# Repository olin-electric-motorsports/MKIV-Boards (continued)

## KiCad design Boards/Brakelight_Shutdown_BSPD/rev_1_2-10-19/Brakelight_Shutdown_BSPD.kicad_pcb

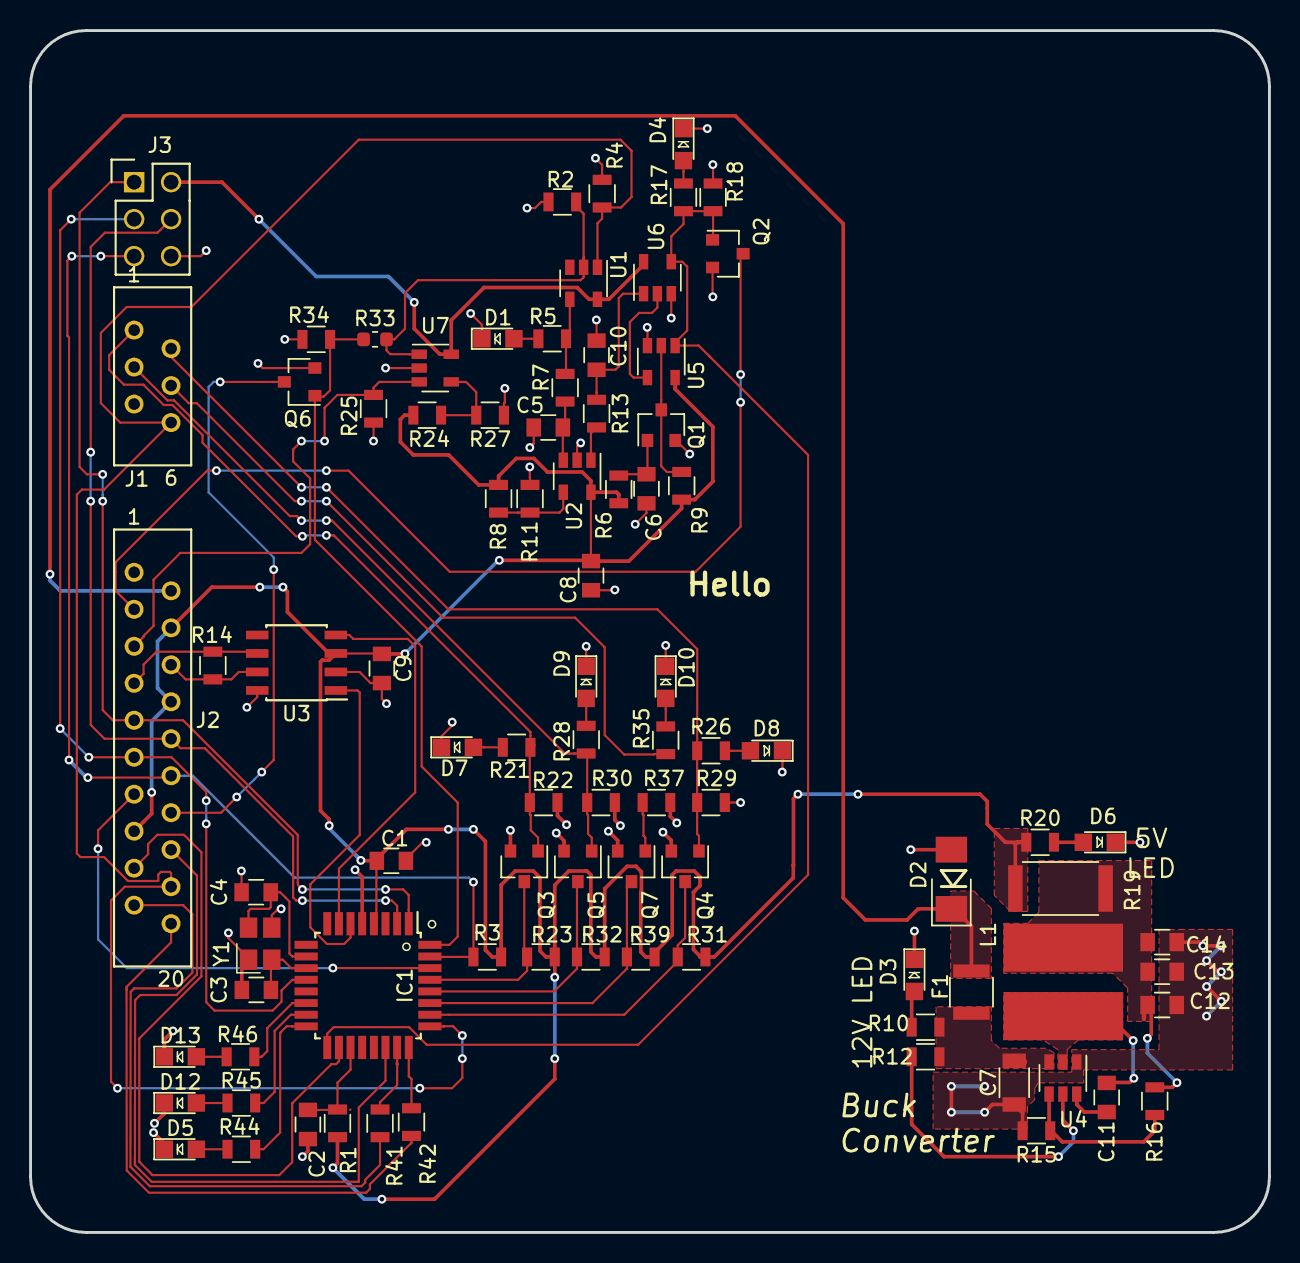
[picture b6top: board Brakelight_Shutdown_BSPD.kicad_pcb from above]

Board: 2 copper layers, 85.1 x 82.6 mm, 89 parts (0 on the bottom side), 65 nets.

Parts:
C1, C6, C8, C9, C11, C14: C_0.1uF; C_0805_OEM
C2: C_100pF; C_0805_OEM
C3, C4: C_30pF; C_0805_OEM
C5: C_10uF; C_0805_OEM
C7: C_22uF; C_1206_OEM
C10, C13: C_1uF; C_0805_OEM
C12: C_47uF; C_0805_OEM
D1, D3, D4, D5, D6, D7, D8, D9, D10, D12, D13: LED_0805; LED_0805_OEM
D2: D_Zener_18V; DO-214AA
F1: 500mA; Fuse_1210
IC1: ATMEGA16M1; TQFP-32_7x7mm_Pitch0.8mm
J1: MM_F_RA_06; micromatch_female_ra_6
J2: MM_F_RA_20; micromatch_female_ra_20
J3: CONN_02X03; Pin_Header_Straight_2x03
L1: L_4.7uH; 4.7uH_Inductor_OEM
Q1, Q2, Q3, Q4, Q5, Q6, Q7: SSM3K333R; SOT-23F
R1: R_100; R_0805_OEM
R2, R4, R9, R22, R29, R30, R37: R_100K; R_0805_OEM
R3, R12, R15: R_10k; R_0805_OEM
R5, R14, R17, R20, R41, R42, R44, R45, R46: R_200; R_0805_OEM
R6, R8, R11, R13, R18, R23, R24, R25, R27, R31, R32, R34, R39: R_10K; R_0805_OEM
R7: R_71.5K; R_0805_OEM
R10: R_1k; R_0805_OEM
R16: R_51.1k; R_0805_OEM
R19: R_0_Jumper; R_2512_OEM
R21, R26, R28, R35: R_1K; R_0805_OEM
R33: R_0; R_0603_1608Metric
U1: SN74LVC1G08; SOT-23-5_OEM
U2, U7: MCP6001; SOT-23-5_OEM
U3: CAN_Transceiver; SOIC-8_3.9x4.9mm_Pitch1.27mm_OEM
U4: TPS561201; SOT-23-6_OEM
U5, U6: SN74LVC1G02; SOT-23-5_OEM
Y1: Crystal_SMD; Crystal_SMD_FA238

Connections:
+12V: D2.1, F1.1, J2.2
/12V_Fused: C7.1, F1.2, R10.1, R12.1, U4.3
/BSPD_Current_Sense: IC1.25, J1.6, J2.18, R4.2, U1.1
/BSPD_Relay: J2.3, Q2.3
/BSPD_Relay_Sense: IC1.17, Q2.1, R17.1, R18.1, U5.1, U6.4
/Brake_Pressure-: IC1.18, J2.17
/Brake_Pressure_Sense: IC1.22, J2.16
/Brake_Switch-: J2.5, R25.2, U7.3
/Brake_Switch_Pressed: R2.1, R33.2, U1.2, U7.1
/Brakelight_Gate: IC1.32, Q6.1, R33.1, R34.1
/Brakelight_LSD: J2.14, Q6.3
/CAN_high: J2.6, R14.1, U3.7
/CAN_low: J2.7, R14.2, U3.6
/Cooling_Pump_LSD_n: IC1.30, J2.13
/LED_1: IC1.14, R46.1
/LED_2: IC1.15, R45.1
/LED_3: IC1.16, R44.1
/MISO: IC1.1, J2.9, J3.1
/MOSI: IC1.2, J2.10, J3.4
/RESET: IC1.31, J2.12, J3.5, R3.2
/RJ45_LED1: J2.19, R41.1
/RJ45_LED2: J2.20, R42.2
/RXCAN: IC1.7, U3.4
/SCK: IC1.12, J2.11, J3.3
/SS_BSPD_Pin: IC1.28, Q5.3, R32.2
/SS_E-Stop_Pin: IC1.26, Q4.3, R31.2
/SS_Main_Shutdown_Pin: IC1.29, Q3.3, R23.2
/SS_TSMS_Pin: IC1.27, Q7.3, R39.2
/Shutdown_Sense_BSPD: J1.3, Q5.1, R28.1, R30.1
/Shutdown_Sense_Estop: J1.2, Q4.1, R26.1, R29.1
/Shutdown_Sense_GLVMS: J1.1, Q3.1, R21.1, R22.1
/Shutdown_Sense_TSMS: J1.4, Q7.1, R35.1, R37.1
/TXCAN: IC1.6, U3.1
GND: C1.2, C2.2, C3.2, C4.2, C5.2, C6.2, C7.2, C8.2, C9.2, C10.2, C12.2, C13.2, C14.2, D1.1, D2.2, D3.1, D4.1, D5.1, D6.1, D7.1, D8.1, D9.1, D10.1, D12.1, D13.1, IC1.5, IC1.20, J2.1, J3.6, Q1.2, Q2.2, Q3.2, Q4.2, Q5.2, Q6.2, Q7.2, R2.2, R4.1, R11.2, R15.2, R18.2, R22.2, R25.1, R27.1, R29.2, R30.2, R34.2, R37.2, U1.3, U2.2, U3.2, U3.8, U4.1, U5.3, U6.3, U7.2, Y1.2, Y1.4
unnamed: C2.1, IC1.19, R1.2
unnamed: C3.1, IC1.11, Y1.1
unnamed: C4.1, IC1.10, Y1.3
unnamed: C5.1, R7.2, U2.3
unnamed: C6.1, Q1.1, R6.2
unnamed: C10.1, R13.1, U6.1
unnamed: C11.1, U4.6
unnamed: C11.2, L1.1, U4.2
unnamed: C12.1, C13.1, C14.1, L1.2, R16.2, R19.2
unnamed: D1.2, R5.2
unnamed: D3.2, R10.2
unnamed: D4.2, R17.2
unnamed: D5.2, R44.2
unnamed: D6.2, R20.2
unnamed: D7.2, R21.2
unnamed: D8.2, R26.2
unnamed: D9.2, R28.2
unnamed: D10.2, R35.2
unnamed: D12.2, R45.2
unnamed: D13.2, R46.2
unnamed: IC1.23, R41.2
unnamed: IC1.24, R42.1
unnamed: Q1.3, R9.1, U5.2
unnamed: R5.1, R7.1, U1.4
unnamed: R8.2, R11.1, U2.4
unnamed: R12.2, U4.5
unnamed: R13.2, U2.1
unnamed: R15.1, R16.1, U4.4
unnamed: R24.1, R27.2, U7.4
unnamed: U5.4, U6.2
VCC: C1.1, C8.1, C9.1, IC1.4, J2.4, J2.8, J2.15, J3.2, R1.1, R3.1, R6.1, R8.1, R9.2, R19.1, R20.1, R23.1, R24.2, R31.1, R32.1, R39.1, U1.5, U2.5, U3.3, U5.5, U6.5, U7.5

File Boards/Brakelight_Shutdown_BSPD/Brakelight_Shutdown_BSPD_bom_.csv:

Component,Description,Part,References,Value,Footprint,Quantity Per PCB,Datasheet,Package,MPN,MFN,PurchasingLink
1,"Capacitor, 0.1uF, 50V, 5%, 0805",C_0.1uF,C1 C6 C8 C9 C11 C14,C_0.1uF,C_0805_OEM,6,http://datasheets.avx.com/X7RDielectric.pdf,Value,478-3352-1-ND,Digi-Key DK,https://www.digikey.com/products/en?keywords=478-3352-1-ND
2,"Capacitor, 100pF, 50V, 5%, 0805",C_100pF,C2,C_100pF,C_0805_OEM,1,https://content.kemet.com/datasheets/KEM_C1003_C0G_SMD.pdf,Value,399-1122-1-ND,Digi-Key,https://www.digikey.com/product-detail/en/kemet/C0805C101J5G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
3,"Capacitor, 10uF, 10V, 10%, 0805",C_10uF,C5,C_10uF,C_0805_OEM,1,http://www.samsungsem.com/kr/support/product-search/mlcc/__i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,,1276-1052-1-ND,DK,https://www.digikey.com/product-detail/en/samsung-electro-me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
4,"Capacitor, 1uF, 25V, 10%, 0805",C_1uF,C10 C13,C_1uF,C_0805_OEM,2,http://www.samsungsem.com/kr/support/product-search/mlcc/__i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,Value,1276-2887-1-ND 478-10487-1-ND,DK Digi-Key,https://www.digikey.com/product-detail/en/samsung-electro-me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 https://www.digikey.com/product-detail/en/avx-corporation/08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
5,"Capacitor, 22uF, 16V, 20%, 1206",C_22uF,C7,C_22uF,C_1206_OEM,1,http://www.samsungsem.com/kr/support/product-search/mlcc/__i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,Value,1276-2725-1-ND,Digi-Key,https://www.digikey.com/products/en?keywords=1276-2725-1-ND
6,"Capacitor, 30pF, 50V, 5%, 0805",C_30pF,C3 C4,C_30pF,C_0805_OEM,2,https://media.digikey.com/pdf/Data%20Sheets/Samsung%20PDFs/C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,Value,1276-1130-1-ND,Digi-Key,https://www.digikey.com/product-detail/en/samsung-electro-me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
7,"Capacitor, 47uF, 6.3V, 20%, 0805",C_47uF,C12,C_47uF,C_0805_OEM,1,http://www.yuden.co.jp/productdata/catalog/en/mlcc_all_e.pdf,Value,587-4280-1-ND,Digi-Key,https://www.digikey.com/product-detail/en/taiyo-yuden/JMK212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
8,"Diode, Zener, 18V, 5W, 5%",D_Zener_18V,D2,D_Zener_18V,DO-214AA,1,http://www.mccsemi.com/up_pdf/SMBJ5338B-SMBJ5388B(SMB).pdf,DO-214AA (SMB),SMBJ5355B-TPMSCT-ND,Digi-Key,https://www.digikey.com/products/en?keywords=SMBJ5355B-TPMSCT-ND
9,"LED, Green, 2.2V, 20mA, 0805",LED_0805,D1 D3 D4 D5 D6 D7 D8 D9 D10 D11 D12 D13,LED_0805,LED_0805_OEM,12,http://www.osram-os.com/Graphics/XPic9/00078860_0.pdf,Value,475-1410-1-ND,DK Digi-Key,https://www.digikey.com/products/en?keywords=475-1410-1-ND
10,"Fuse, PTC, 500mA, 16V, 1210",F_500mA_16V,F1,500mA,Fuse_1210,1,https://belfuse.com/resources/CircuitProtection/datasheets/0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,Value,507-1786-1-ND,Digi-Key,https://www.digikey.com/product-detail/en/bel-fuse-inc/0ZCH0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
11,"Microcontroller, 8-bit, 1KB RAM, 16KB Flash",ATMEGA16M1,IC1,ATMEGA16M1,TQFP-32_7x7mm_Pitch0.8mm,1,http://www.atmel.com/Images/Atmel-8209-8-bit%20AVR%20ATmega1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,Value,ATMEGA16M1-AU-ND,Digi-Key,https://www.digikey.com/product-detail/en/atmel/ATMEGA16M1-A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
12,"Connector header through hole 2x3 0.100"" (2.54mm)",CONN_02X03,J3,CONN_02X03,Pin_Header_Straight_2x03,1,http://portal.fciconnect.com/Comergent//fci/drawing/67996.pdf,Value,609-3234-ND,Digi-Key,https://www.digikey.com/product-detail/en/amphenol-fci/67997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
13,Micro-MaTch connector 6 pin female right angle,MM_F_RA_06,J1,MM_F_RA_06,micromatch_female_ra_6,1,http://www.te.com/commerce/DocumentDelivery/DDEController?Ac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,,338070-6,TE,http://www.te.com/usa-en/product-338070-6.html
14,Micro-MaTch connector 20 pin female right angle,MM_F_RA_20,J2,MM_F_RA_20,micromatch_female_ra_20,1,http://www.te.com/commerce/DocumentDelivery/DDEController?Ac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,,2-338070-0,TE,http://www.te.com/usa-en/product-2-338070-0.html
15,"Inductor, 4.7uH, 4.4A, 25mOhm, 20%",L_4.7uH,L1,L_4.7uH,4.7uH_Inductor_OEM,1,https://product.tdk.com/info/en/documents/wdcatalog/withdraw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,Value,445-6583-1-ND,Digi-Key,https://www.digikey.com/product-detail/en/tdk-corporation/VL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
16,"MOSFET, N-channel, 30V, 6A",SSM3K333R,Q1 Q2 Q3 Q4 Q5 Q6 Q7,SSM3K333R,SOT-23F,7,https://drive.google.com/drive/folders/0B-V-iZf33Y4GNzhDQTJZanJRbVk,,SSM3K333RLFCT-ND,DK,https://www.digikey.com/product-detail/en/toshiba-semiconduc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
17,"Resistor, 0 ohm jumper, 0.1W, 0603",R_0,R33,R_0,R_0603_1608Metric,1,http://industrial.panasonic.com/www-cgi/jvcr13pz.cgi?E+PZ+3+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,,P0.0GCT-ND,DK,https://www.digikey.com/product-detail/en/panasonic-electron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
18,"Resistor, 0 ohm jumper, 0.1W, 0603",R_0,R19,R_0_Jumper,R_2512_OEM,1,http://www.te.com/commerce/DocumentDelivery/DDEController?Ac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,Value,A121322CT-ND,Digi-Key,https://www.digikey.com/products/en?keywords=A121322CT-ND
19,"Resistor, 100, 0.25W, 1%, 0805",R_100,R1,R_100,R_0805_OEM,1,https://www.seielect.com/Catalog/SEI-rncp.pdf,Value,RNCP0805FTD100RCT-ND,Digi-Key,https://www.digikey.com/products/en?keywords=RNCP0805FTD100RCT-ND
20,"Resistor, 100K, 0.125W, 1%, 0805",R_100K,R2 R4 R9 R22 R29 R30 R37,R_100K,R_0805_OEM,7,https://industrial.panasonic.com/cdbs/www-data/pdf/RDA0000/A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,,P100KCCT-ND,DK,https://www.digikey.com/product-detail/en/panasonic-electron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
21,"Resistor, 10K, 0.25W, 1%, 0805",R_10K,R3 R6 R8 R11 R13 R18 R23 R24 R25 R27 R31 R32 R34 R39,R_10k,R_0805_OEM,14,http://www.bourns.com/data/global/pdfs/CRS.pdf,Value,CRS0805-FX-1002ELFCT-ND,Digi-Key DK,https://www.digikey.com/products/en?keywords=CRS0805-FX-1002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
22,"Resistor, 10K, 5W, 1%, Axial",R_10K_HV,R12 R15,R_10k,R_0805_OEM,2,http://www.bourns.com/data/global/pdfs/CRS.pdf,Value,CRS0805-FX-1002ELFCT-ND,Digi-Key,https://www.digikey.com/products/en?keywords=CRS0805-FX-1002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
23,,R_1K-formula,R36,R_1K-formula,R_0805_OEM,1,https://www.seielect.com/Catalog/SEI-rncp.pdf,,RNCP0805FTD1K00CT-ND,DK,https://www.digikey.com/products/en?keywords=RNCP0805FTD1K00CT-ND
24,"Resistor, 1K, 0.25W, 1%, 0805",R_1K,R10 R21 R26 R28 R35,R_1k,R_0805_OEM,5,https://www.seielect.com/Catalog/SEI-rncp.pdf,Value,RNCP0805FTD1K00CT-ND,Digi-Key DK,https://www.digikey.com/products/en?keywords=RNCP0805FTD1K00CT-ND
25,"Resistor, 200, 0.125W, 5%, 0805",R_200,R5 R14 R17 R20 R41 R42 R44 R45 R46,R_200,R_0805_OEM,9,https://www.seielect.com/Catalog/SEI-RMCF_RMCP.pdf,Value,RMCF0805JT200RCT-ND,DK Digi-Key,https://www.digikey.com/products/en?keywords=RMCF0805JT200RCT-ND
26,"Resistor, 51.1K, 0.125W, 1%, 0805",R_51.1K,R16,R_51.1k,R_0805_OEM,1,http://www.yageo.com.tw/exep/pages/download/literatures/PYu-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,Value,311-51.1KCRCT-ND,Digi-Key,https://www.digikey.com/products/en?keywords=311-51.1KCRCT-ND
27,"Resistor, 1.07K, 0.125W, 0.1%, 0805",R_1.07K,R7,R_71.5K,R_0805_OEM,1,https://industrial.panasonic.com/cdbs/www-data/pdf/RDM0000/A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,,P1.07KDACT-ND,DK,
28,"High speed CAN transceiver, 1Mb/s",MCP2561-E_SN,U3,CAN_Transceiver,SOIC-8_3.9x4.9mm_Pitch1.27mm_OEM,1,http://www.microchip.com/mymicrochip/filehandler.aspx?ddocna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,Value,MCP2561-E/SN-ND,Digi-Key,https://www.digikey.com/products/en?keywords=mcp2561-e%2Fsn
29,"Op-amp, general purpose",MCP6001,U2 U7,MCP6001,SOT-23-5_OEM,2,http://ww1.microchip.com/downloads/en/DeviceDoc/21733j.pdf,,MCP6001T-I/OTCT-ND,DK,https://www.digikey.com/product-detail/en/microchip-technolo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
30,Single channel positive logic NOR gate,SN74LVC1G02,U5 U6,SN74LVC1G02,SOT-23-5_OEM,2,http://www.ti.com/lit/ds/symlink/sn74lvc1g02.pdf,,296-11598-1-ND,DK,https://www.digikey.com/product-detail/en/texas-instruments/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
31,Single channel positive logic AND gate,SN74LVC1G08,U1,SN74LVC1G08,SOT-23-5_OEM,1,http://www.ti.com/lit/ds/symlink/sn74lvc1g08.pdf,,296-11602-1-ND,DK,https://www.digikey.com/product-detail/en/texas-instruments/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
32,"Buck converter, 4.5-17V input, adj 0.76-7V output, 1A, 580kHz",TPS561201,U4,TPS561201,SOT-23-6_OEM,1,http://www.ti.com/lit/ds/symlink/tps561201.pdf,Value,TPS561201,Digi-Key,https://www.digikey.com/products/en?keywords=296-46928-1-ND
33,CRYSTAL 16.0000MHZ 18PF SMD,Crystal_SMD,Y1,Crystal_SMD,Crystal_SMD_FA238,1,https://support.epson.biz/td/api/doc_check.php?dl=brief_FA-2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,Value,SER3686CT-ND,Digi-Key,https://www.digikey.com/products/en?keywords=SER3686CT-ND





Component Groups:,33
Component Count:,91
Fitted Components:,91
Number of PCBs:,1
Total components:,91
Schematic Version:,
Schematic Date:,
BoM Date:,Mon 04 Mar 2019 08:26:31 PM EST
Schematic Source:,/home/jerry/Desktop/Formula/MKIV-Boards/Boards/Brakelight_Shutdown_BSPD/Brakelight_Shutdown_BSPD.sch
KiCad Version:,Eeschema 5.0.2-bee76a0~70~ubuntu18.04.1
